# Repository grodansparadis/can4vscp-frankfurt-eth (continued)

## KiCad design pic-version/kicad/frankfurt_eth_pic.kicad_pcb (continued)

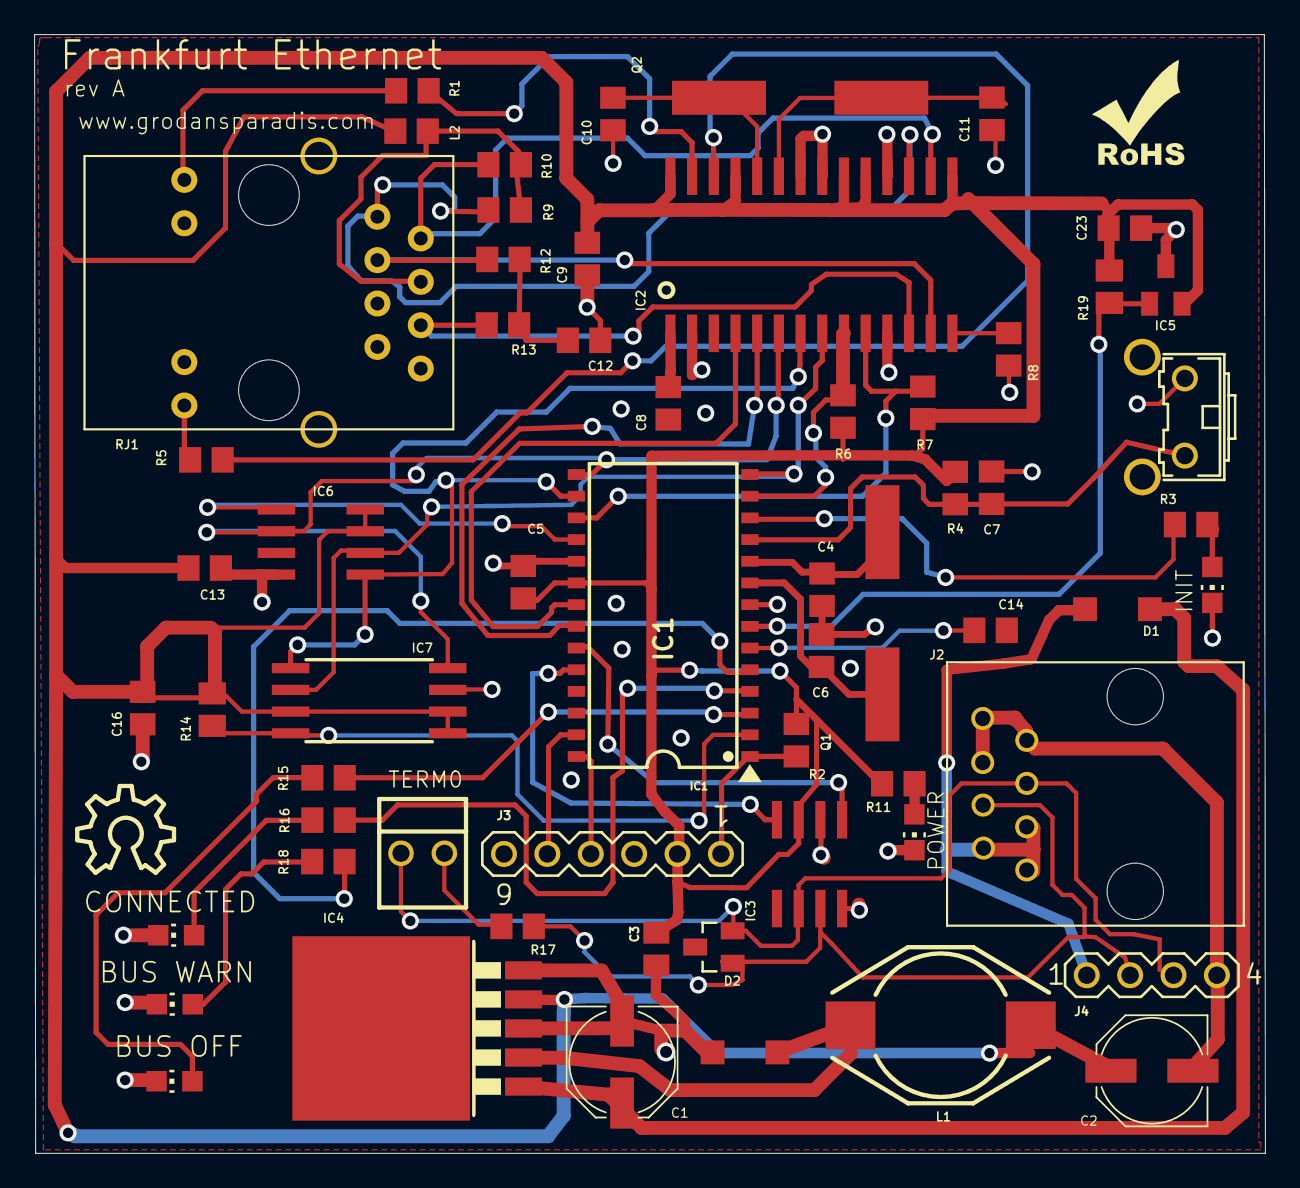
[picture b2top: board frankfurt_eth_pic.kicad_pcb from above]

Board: 6 copper layers, 72.1 x 65.5 mm, 62 parts (0 on the bottom side), 50 nets.

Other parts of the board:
U$1: ROHS_SILK
U$2: OSHW_10X200_NOTEXT

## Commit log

2015-08-17 Initial check in after freedom day
2015-08-17 Changed license to Artistic License 3.0
2015-08-26 Added first version of hardware board
2015-08-26 Ignoring temp files
2015-08-26 Removed old folders
2015-08-28 Edit
2015-08-31 Started ARM version
2015-08-31 Routed
2015-09-01 Clean
2015-09-01 Removed extra status LED's
2015-09-01 edit text layer
2015-09-01 Renamed PIC version
2015-09-02 Added Gerbers
2015-09-02 Removed unused file
2015-09-02 Moved out R14 a bit
2015-09-02 Updated rev texts
2015-09-02 Added board and schema pictures
2015-09-15 Added some info
2015-09-15 Changed a link
2015-09-21 Increase width of vcc for uart connector
2015-09-25 New Gerbers
2015-10-20 Changed layer for info text on pic board
2015-11-13 Rearranged folders
2015-12-17 Updated readme and license
2016-04-04 Changed value of C14 to 10uF
2023-03-03 Added eps32 version
2023-03-06 ESP32 version 1 preliminary done
2023-03-06 Added history file
2023-03-06 Fixed README
2023-03-06 Added pdf schemas for poe version
2023-03-07 Added readme's
2023-03-07 Added link to pcbway
2023-03-07 Added pcbway logo
2023-03-07 Fixed spellig errors
2023-04-25 Added POE version
2025-09-19 Translated schemas to KiCad format
2025-09-19 Added som inital level II build code
2025-09-30 /home/akhe/development/VSCP/can4vscp-odessa/LICENSE
2026-01-28 Updated copyright year
2026-05-05 Rearranged
2026-05-05 Updated license to CERN
